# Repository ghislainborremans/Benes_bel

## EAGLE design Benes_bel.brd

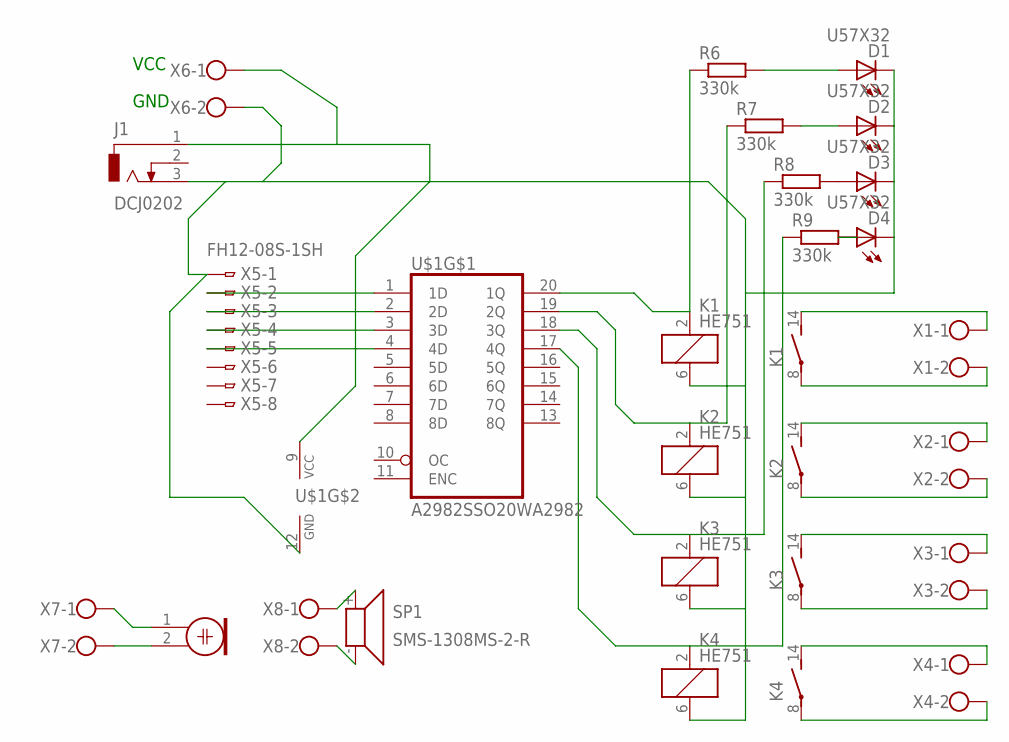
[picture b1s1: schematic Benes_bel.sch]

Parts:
D1, D2, D3, D4: U57X32
J1: DCJ0202
K1, K2, K3, K4: HE751
M1: ELECTRET_MICROPHON-WM-61B; WM-61B
R6, R7, R8, R9: 330k; 0207/12
SP1: SMS-1308MS-2-R
U$1: A2982SSO20WA2982; SO20W
X1, X2, X3, X4, X6, X7, X8: W237-102
X5: FH12-08S-1SH

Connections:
unnamed: U$1.1 (1D), X5.2
unnamed: U$1.2 (2D), X5.3
unnamed: U$1.3 (3D), X5.4
unnamed: U$1.4 (4D), X5.5
unnamed: K2.2 (1), R7.1, U$1.19 (2Q)
unnamed: SP1.+ (1), X8.1
unnamed: SP1.- (2), X8.2
unnamed: M1.1, X7.1
unnamed: M1.2, X7.2
unnamed: K1.14 (S), X1.1
unnamed: K1.8, X1.2
unnamed: K2.14 (S), X2.1
unnamed: K2.8, X2.2
unnamed: K3.14 (S), X3.1
unnamed: K3.8, X3.2
unnamed: K4.14 (S), X4.1
unnamed: K4.8, X4.2
unnamed: K3.2 (1), R8.1, U$1.18 (3Q)
unnamed: K4.2 (1), R9.1, U$1.17 (4Q)
unnamed: D1.K (C), D2.K (C), D3.K (C), D4.K (C), J1.3, K1.6 (2), K2.6 (2), K3.6 (2), K4.6 (2), U$1.12 (GND), X5.1, X6.2
unnamed: J1.1, U$1.9 (VCC), X6.1
unnamed: K1.2 (1), R6.1, U$1.20 (1Q)
unnamed: D4.A, R9.2
unnamed: D1.A, R6.2
unnamed: D2.A, R7.2
unnamed: D3.A, R8.2

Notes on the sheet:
GND
VCC

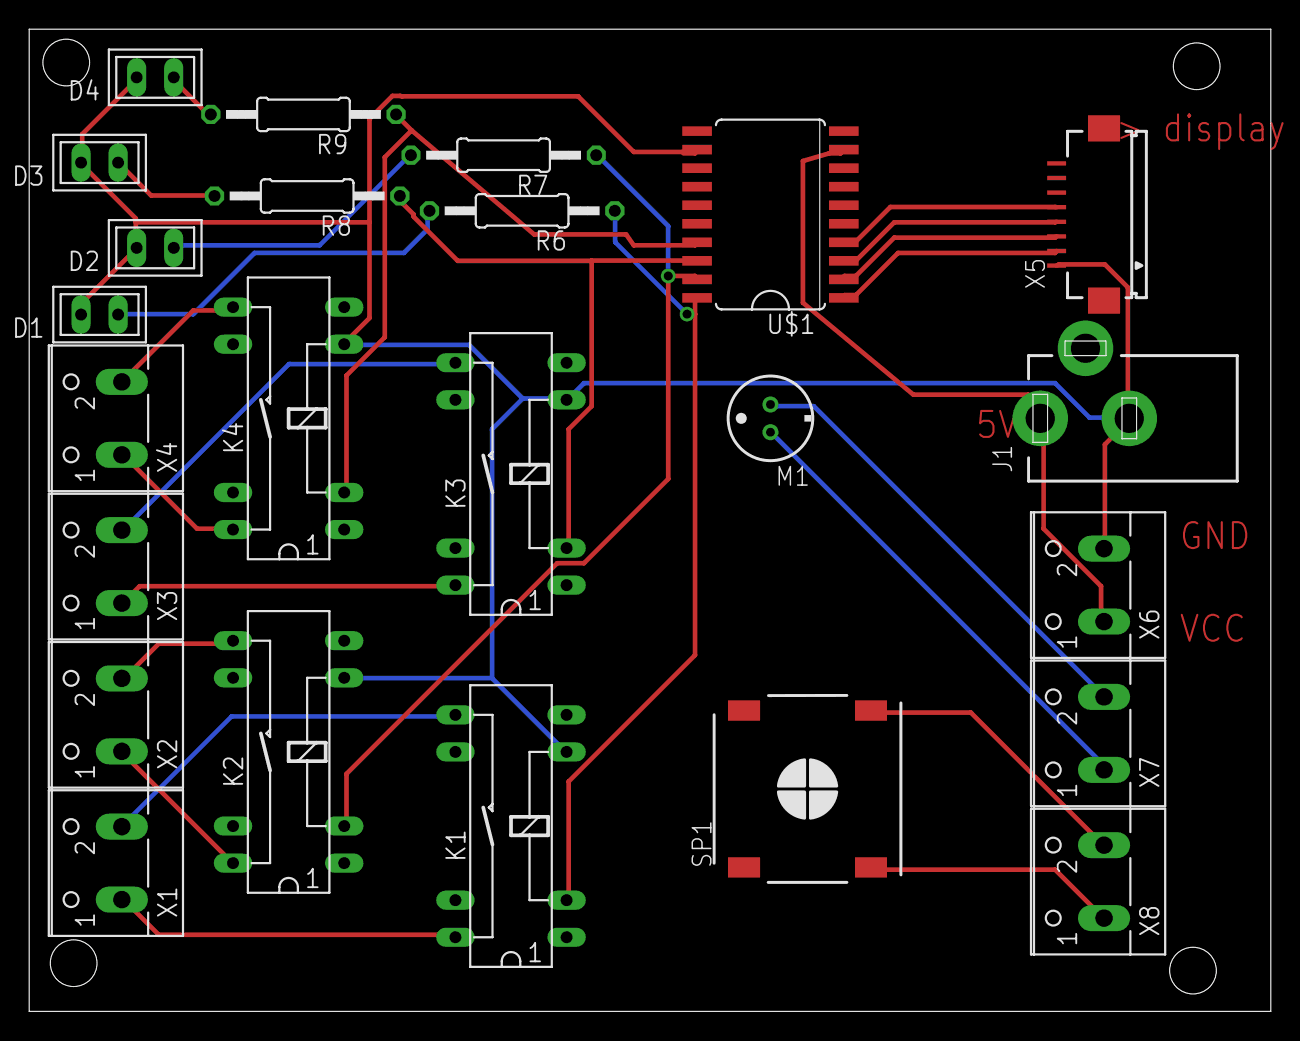
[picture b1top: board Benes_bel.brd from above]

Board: 2 copper layers, 85.1 x 67.3 mm, 24 parts (0 on the bottom side), 26 nets.

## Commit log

2016-10-07 Opstart Benes_bel in Github
2016-10-07 Aanpassing van Benes_bel
    dikkere lijnen, groter afstand voor frezen
2016-10-08 Uitvoering voor het frezen
2016-10-08 flexi en enroute gemaakt
    te veel werk om gemakkelijk te zijn
2016-10-11 HMI toegevoegd voor Nextion
2016-10-11 test voor commit
2016-10-11 test git 2
2016-10-14 aanpassing met extra leds als controle tracks op 2 lagen Gerber files
2016-10-20 bel soft met timer+boodschap
2016-10-22 Bord werkt op eerste pcb ontbreken 3 draden in de schema's en de prod files is dit aangepast.
2016-10-22 toevoeging van gerb274sx.cam file voor het gemakkelijk aanmaken van de gerber files Camprocessor->open Job-> gerber-jeremy
2016-10-23 correctie bord: groter gaten vr DC Jack toevoeging van vcc naar display leds meer ruimte
2016-10-27 Beeld 180° gedraaid in kast , toegevoegd, edit afwezigheids tekst bel nr weg, 1 extra lijn onder naam
2016-10-27 tft file toegevoegd
2016-10-27 nextion app toegevoegd als archeif
2016-11-01 200ms tijd contact gesloten ipv 10 pio0-4=0 bij begin
2016-11-01 slider toegevoegd voor delay rond de 250 is ok voor het contact naar het alarm
2016-11-24 contact tijd verhoogd tot 10000 initieel op 500
2016-11-24 met high level switch + speaker + mic
    eerste versie was met een low level switch
    nu met met darlington (npn+pnp)
2016-12-08 met namen op bel
2016-12-14 wachttijd tussen 2 bellen >= anti dither tijd op NVR
2017-10-12 Saldi per default toegevoegd + tijd van contact gesloten = min 500ms
